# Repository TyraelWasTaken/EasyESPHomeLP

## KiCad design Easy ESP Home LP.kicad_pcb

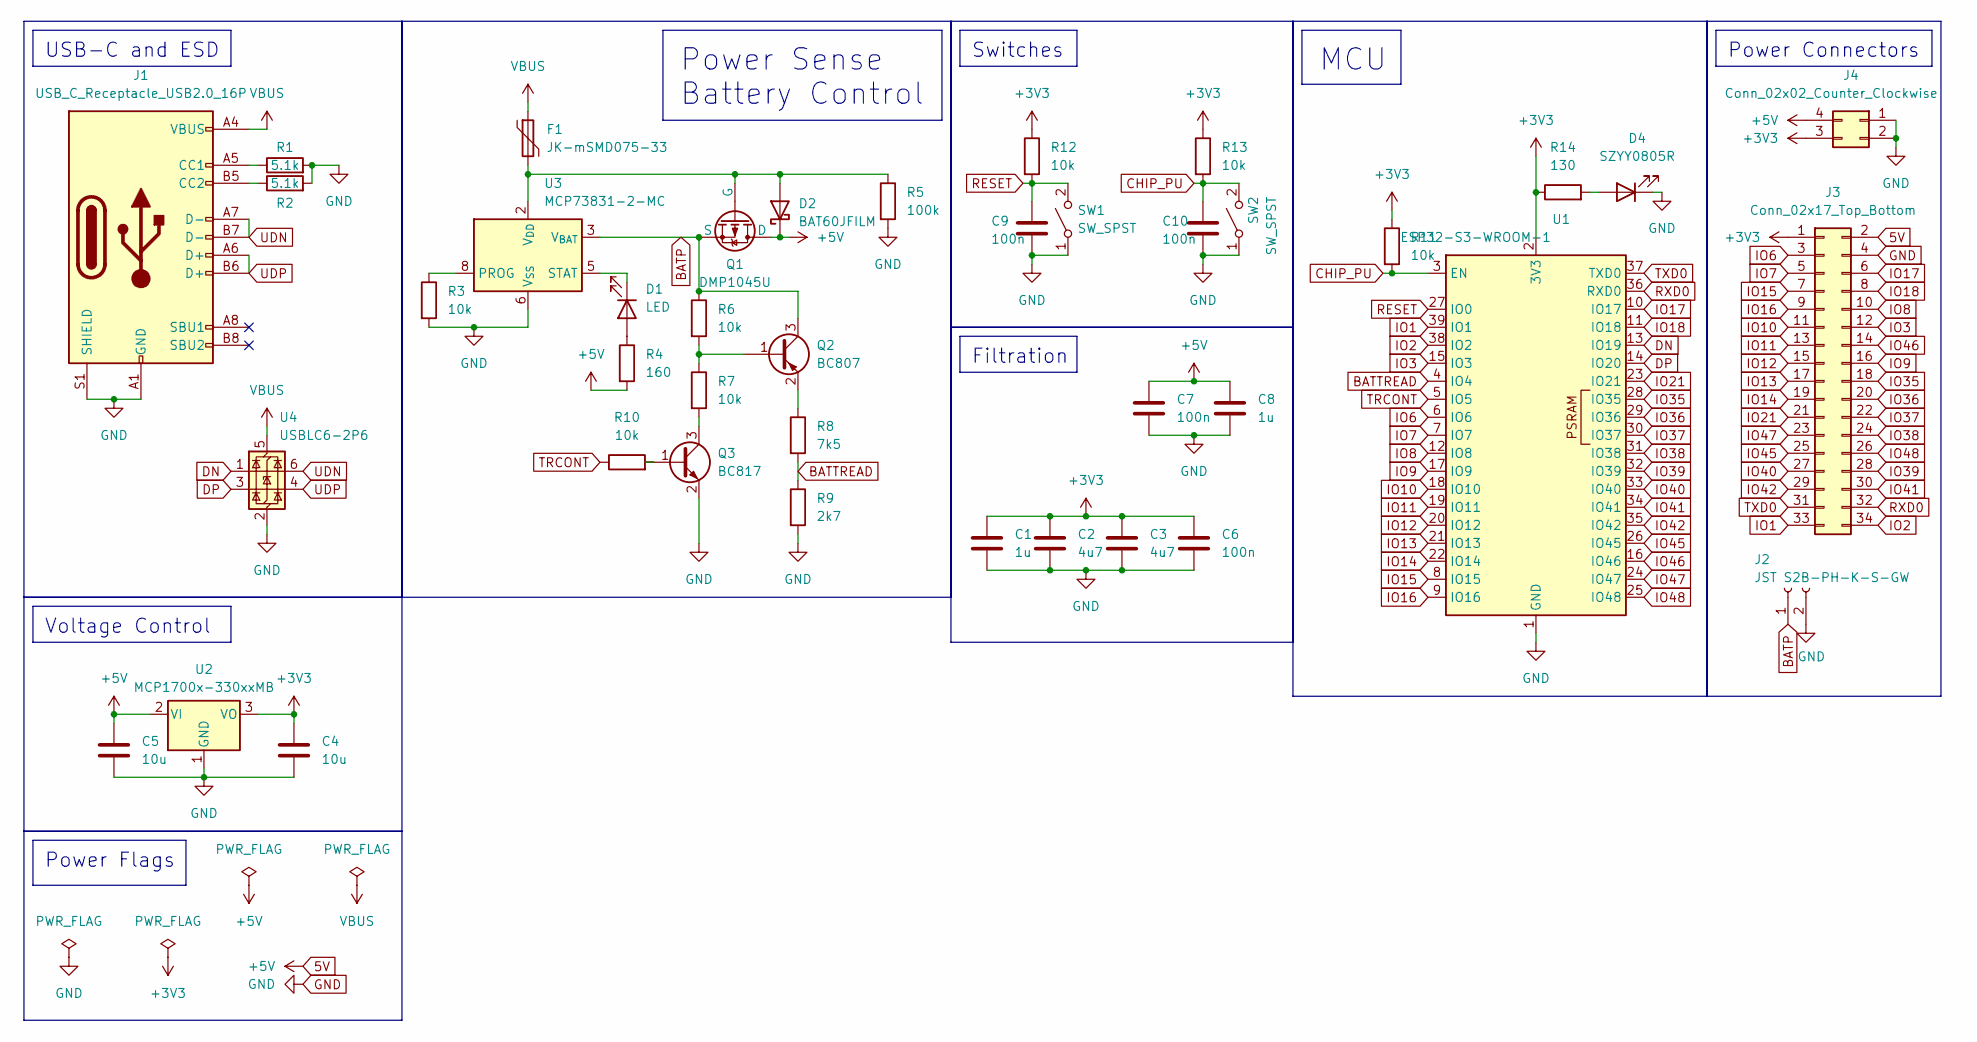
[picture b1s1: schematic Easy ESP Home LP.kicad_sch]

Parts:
C1, C8: 1u; C_0805_2012Metric_Pad1.18x1.45mm_HandSolder
C2, C3: 4u7; C_0805_2012Metric_Pad1.18x1.45mm_HandSolder
C4, C5: 10u; C_0805_2012Metric_Pad1.18x1.45mm_HandSolder
C6, C7, C9, C10: 100n; C_0805_2012Metric_Pad1.18x1.45mm_HandSolder
D1: LED; LED_0603_1608Metric_Pad1.05x0.95mm_HandSolder
D2: BAT60JFILM; D_SOD-323_HandSoldering
D4: SZYY0805R; LED_0805_2012Metric_Pad1.15x1.40mm_HandSolder
F1: JK-mSMD075-33; Fuse_1812_4532Metric_Pad1.30x3.40mm_HandSolder
J1: USB_C_Receptacle_USB2.0_16P; USB_C_Receptacle_G-Switch_GT-USB-7010ASV
J2: JST S2B-PH-K-S-GW; JST_PH_S2B-PH-SM4-TB_1x02-1MP_P2.00mm_Horizontal
J3: Conn_02x17_Top_Bottom; PinHeader_2x17_P2.54mm_Vertical
J4: Conn_02x02_Counter_Clockwise; PinHeader_2x02_P2.54mm_Vertical
Q1: DMP1045U; SOT-23_Handsoldering
Q2: BC807; SOT-23
Q3: BC817; SOT-23
R1, R2: 5.1k; R_0603_1608Metric_Pad0.98x0.95mm_HandSolder
R3, R6, R7, R10, R11, R12, R13: 10k; R_0603_1608Metric_Pad0.98x0.95mm_HandSolder
R4: 160; R_0603_1608Metric_Pad0.98x0.95mm_HandSolder
R5: 100k; R_0603_1608Metric_Pad0.98x0.95mm_HandSolder
R8: 7k5; R_0603_1608Metric_Pad0.98x0.95mm_HandSolder
R9: 2k7; R_0603_1608Metric_Pad0.98x0.95mm_HandSolder
R14: 130; R_0603_1608Metric_Pad0.98x0.95mm_HandSolder
SW1, SW2: SW_SPST; SW_SPST_SKQG_WithStem
U1: ESP32-S3-WROOM-1
U2: MCP1700x-330xxMB; SOT-89-3
U3: MCP73831-2-MC; DFN-8-1EP_3x2mm_P0.5mm_EP1.7x1.4mm
U4: USBLC6-2P6; SOT-666

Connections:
5V: C5.1, C7.1, C8.1, D2.1 (K), J3.2, J4.4, Q1.1 (D), R4.2, U2.2 (VI)
+3V3: C1.1, C2.1, C3.1, C4.1, C6.1, J3.1, J4.3, R11.1, R12.1, R13.1, R14.1, U1.2 (3V3), U2.3 (VO)
BATP: J2.1, Q1.3 (S), Q2.3 (C), R6.1, U3.3 (V_{BAT}), U3.4 (V_{BAT})
BATTREAD: R8.2, R9.1, U1.4 (IO4)
CHIP_PU: C10.1, R11.2, R13.2, SW2.2 (B), U1.3 (EN)
DN: U1.13 (IO19), U4.1 (I/O1)
DP: U1.14 (IO20), U4.3 (I/O2)
GND: C1.2, C2.2, C3.2, C4.2, C5.2, C6.2, C7.2, C8.2, C9.2, C10.2, D4.1 (K), J1.A1 (GND), J1.A12 (GND), J1.B1 (GND), J1.B12 (GND), J1.S1 (SHIELD), J2.2, J3.4, J4.1, J4.2, Q3.2 (E), R1.2, R2.2, R3.2, R5.2, R9.2, SW1.1 (A), SW2.1 (A), U1.1 (GND), U1.40 (GND), U1.41 (GND), U1.42, U2.1 (GND), U3.6 (V_{SS}), U3.9, U4.2 (GND)
IO1: J3.33, U1.39 (IO1)
IO2: J3.34, U1.38 (IO2)
IO3: J3.12, U1.15 (IO3)
IO6: J3.3, U1.6 (IO6)
IO7: J3.5, U1.7 (IO7)
IO8: J3.10, U1.12 (IO8)
IO9: J3.16, U1.17 (IO9)
IO10: J3.11, U1.18 (IO10)
IO11: J3.13, U1.19 (IO11)
IO12: J3.15, U1.20 (IO12)
IO13: J3.17, U1.21 (IO13)
IO14: J3.19, U1.22 (IO14)
IO15: J3.7, U1.8 (IO15)
IO16: J3.9, U1.9 (IO16)
IO17: J3.6, U1.10 (IO17)
IO18: J3.8, U1.11 (IO18)
IO21: J3.21, U1.23 (IO21)
IO35: J3.18, U1.28 (IO35)
IO36: J3.20, U1.29 (IO36)
IO37: J3.22, U1.30 (IO37)
IO38: J3.24, U1.31 (IO38)
IO39: J3.28, U1.32 (IO39)
IO40: J3.27, U1.33 (IO40)
IO41: J3.30, U1.34 (IO41)
IO42: J3.29, U1.35 (IO42)
IO45: J3.25, U1.26 (IO45)
IO46: J3.14, U1.16 (IO46)
IO47: J3.23, U1.24 (IO47)
IO48: J3.26, U1.25 (IO48)
unnamed: D1.2 (A), R4.1
unnamed: D1.1 (K), U3.5 (STAT)
unnamed: D2.2 (A), F1.2, Q1.2 (G), R5.1, U3.1 (V_{DD}), U3.2 (V_{DD})
unnamed: D4.2 (A), R14.2
unnamed: J1.A5 (CC1), R1.1
unnamed: J1.B5 (CC2), R2.1
unnamed: Q2.1 (B), R6.2, R7.1
unnamed: Q2.2 (E), R8.1
unnamed: Q3.1 (B), R10.2
unnamed: Q3.3 (C), R7.2
unnamed: R3.1, U3.8 (PROG)
RESET: C9.1, R12.2, SW1.2 (B), U1.27 (IO0)
RXD0: J3.32, U1.36 (RXD0)
TRCONT: R10.1, U1.5 (IO5)
TXD0: J3.31, U1.37 (TXD0)
UDN: J1.A7 (D-), J1.B7 (D-), U4.6 (I/O1)
UDP: J1.A6 (D+), J1.B6 (D+), U4.4 (I/O2)
VBUS: F1.1, J1.A4 (VBUS), J1.A9 (VBUS), J1.B4 (VBUS), J1.B9 (VBUS), U4.5 (VBUS)

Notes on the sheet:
USB-C and ESD
Switches
MCU
Voltage Control
Power Sense Battery Control
Power Flags
Power Connectors
Filtration

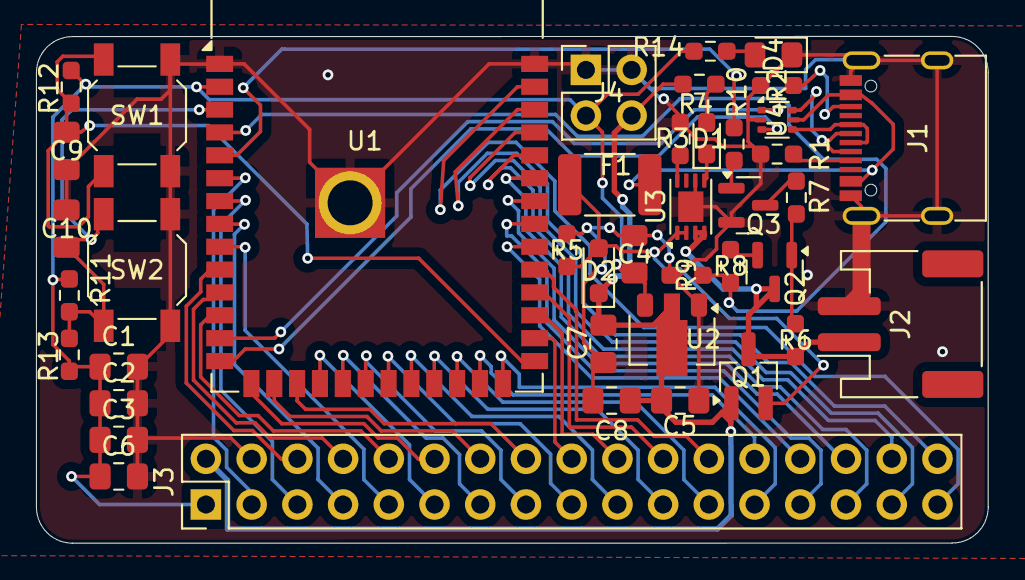
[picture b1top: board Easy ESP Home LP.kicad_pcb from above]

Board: 2 copper layers, 52.9 x 28.2 mm, 41 parts (0 on the bottom side), 55 nets.

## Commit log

2024-11-17 init
